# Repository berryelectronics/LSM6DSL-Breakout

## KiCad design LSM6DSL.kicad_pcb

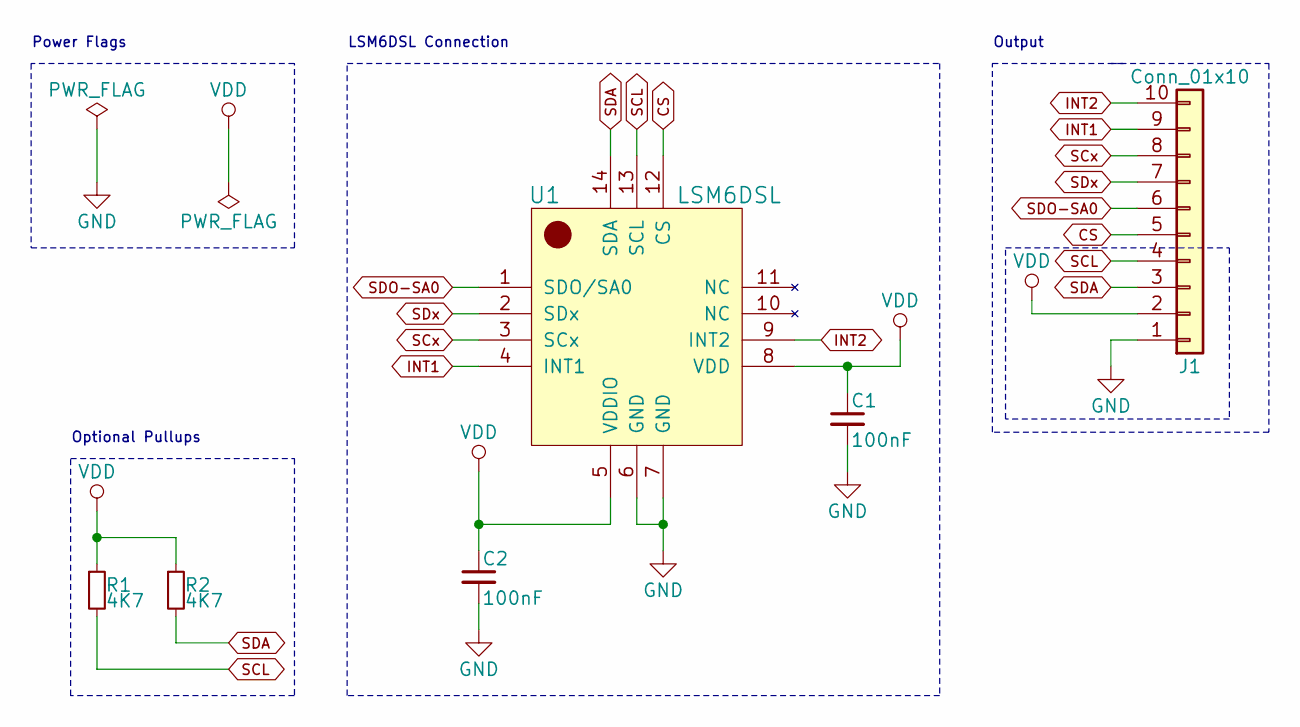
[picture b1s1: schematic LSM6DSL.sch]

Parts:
C1, C2: 100nF; C_0603
J1: Conn_01x10; Pin_Header_Straight_1x10_Pitch2.54mm
R1, R2: 4K7; R_0805
U1: LSM6DSL; LGA-14-2.5x3x0.86

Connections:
CS: J1.5, U1.12 (CS)
GND: C1.2, C2.2, J1.1, U1.6 (GND), U1.7 (GND)
INT1: J1.9, U1.4 (INT1)
INT2: J1.10, U1.9 (INT2)
SCL: J1.4, R1.2, U1.13 (SCL)
SCx: J1.8, U1.3 (SCx)
SDA: J1.3, R2.2, U1.14 (SDA)
SDO-SA0: J1.6, U1.1 (SDO/SA0)
SDx: J1.7, U1.2 (SDx)
VDD: C1.1, C2.1, J1.2, R1.1, R2.1, U1.5 (VDDIO), U1.8 (VDD)

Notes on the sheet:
Optional Pullups
LSM6DSL Connection
Power Flags
Output

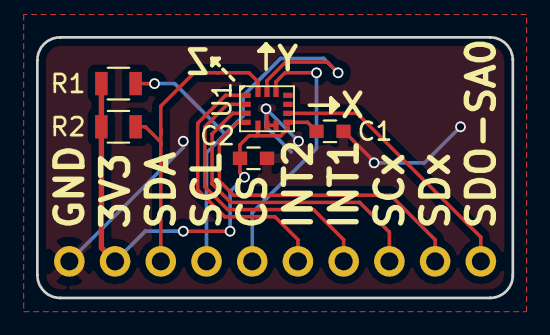
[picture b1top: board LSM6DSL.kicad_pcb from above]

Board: 2 copper layers, 26.4 x 14.5 mm, 6 parts (1 on the bottom side), 10 nets.

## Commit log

2018-03-08 Finished schematic, created LSM6DSL Footprint and Component
2018-03-08 Fixed wrong label INT1
2018-03-08 Finished PCB and Schematic
2018-03-08 Added rounded Edges
2018-03-08 Increased size
2018-03-08 saved changes
2018-03-08 mirroring of back text
2018-03-11 changes in the view
